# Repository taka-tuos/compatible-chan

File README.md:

# compatible-chan
[スタックチャン](https://github.com/stack-chan/stack-chan) 用の自由なCoreモジュール (GPLv3)

# ・ _ ・

# このプロジェクトのスコープ
- スタックチャンのCoreモジュールに自由な選択肢を追加することが目的
- M5Stack系の製品を広範に置き換えるもの**ではない** (スタックチャンに必要な機能のみを実装する)

# FAQ
## Q. M5Stackって「オープンハードウェア」では？
A. 各種ピン仕様や回路図こそオープンではあるが、シェルのCADデータやガーバーファイル、BOM等が公開されていないので「自由」ではない(と自分は考えている)。

## Q. 自由でないと何がダメ？
A. スタックチャンは「サ終とともに死ぬロボットはアカン(意訳)」という思想を含んでいて[^1](https://protopedia.net/prototype/2345)、M5Stackの供給が止まると死ぬ状況はよろしくないはず。  
(実際オンラインに依存していない旧AIBOシリーズでも、部品供給が無いのでバタバタ死んでいる)  
またM5Stackの仕様に縛られる状況でその打開ができないのもよろしくない(よく挙がる例としてはスピーカーとマイクが排他なことなど)

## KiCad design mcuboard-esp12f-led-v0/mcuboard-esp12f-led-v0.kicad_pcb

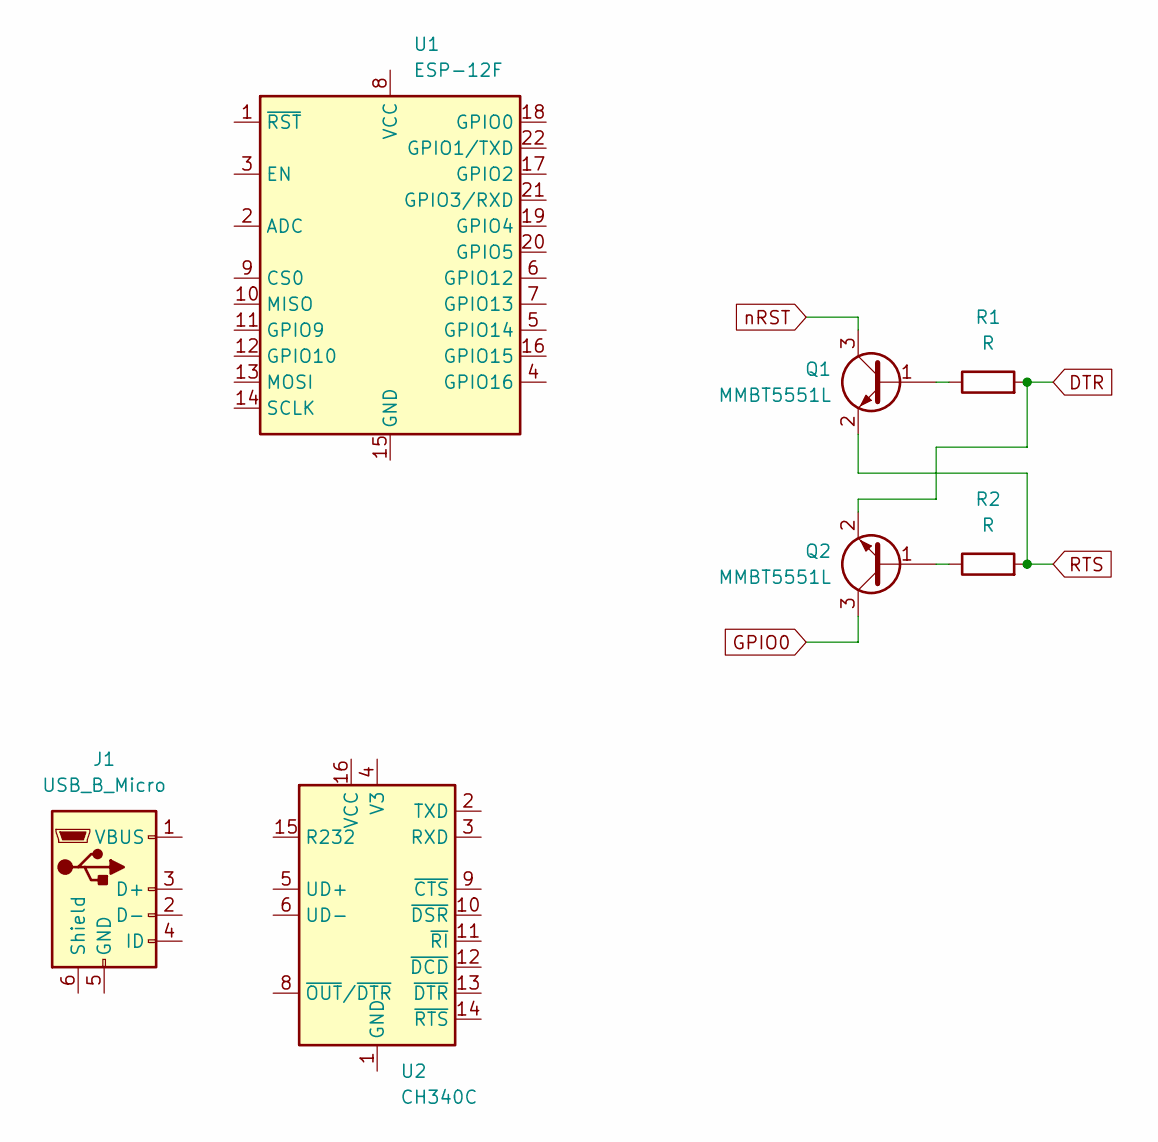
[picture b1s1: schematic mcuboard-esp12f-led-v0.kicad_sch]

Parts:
J1: USB_B_Micro; USB_Micro-B_Wuerth_629105150521
Q1, Q2: MMBT5551L; SOT-23
R1, R2: R; R_0805_2012Metric_Pad1.20x1.40mm_HandSolder
U1: ESP-12F; ESP-12E
U2: CH340C; SOIC-16_3.9x9.9mm_P1.27mm

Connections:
DTR: Q2.2 (E), R1.2
GPIO0: Q2.3 (C)
unnamed: Q1.1 (B), R1.1
unnamed: Q2.1 (B), R2.1
RTS: Q1.2 (E), R2.2
nRST: Q1.3 (C)

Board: 2 copper layers, 7 parts (0 on the bottom side), 4 nets, no tracks yet.

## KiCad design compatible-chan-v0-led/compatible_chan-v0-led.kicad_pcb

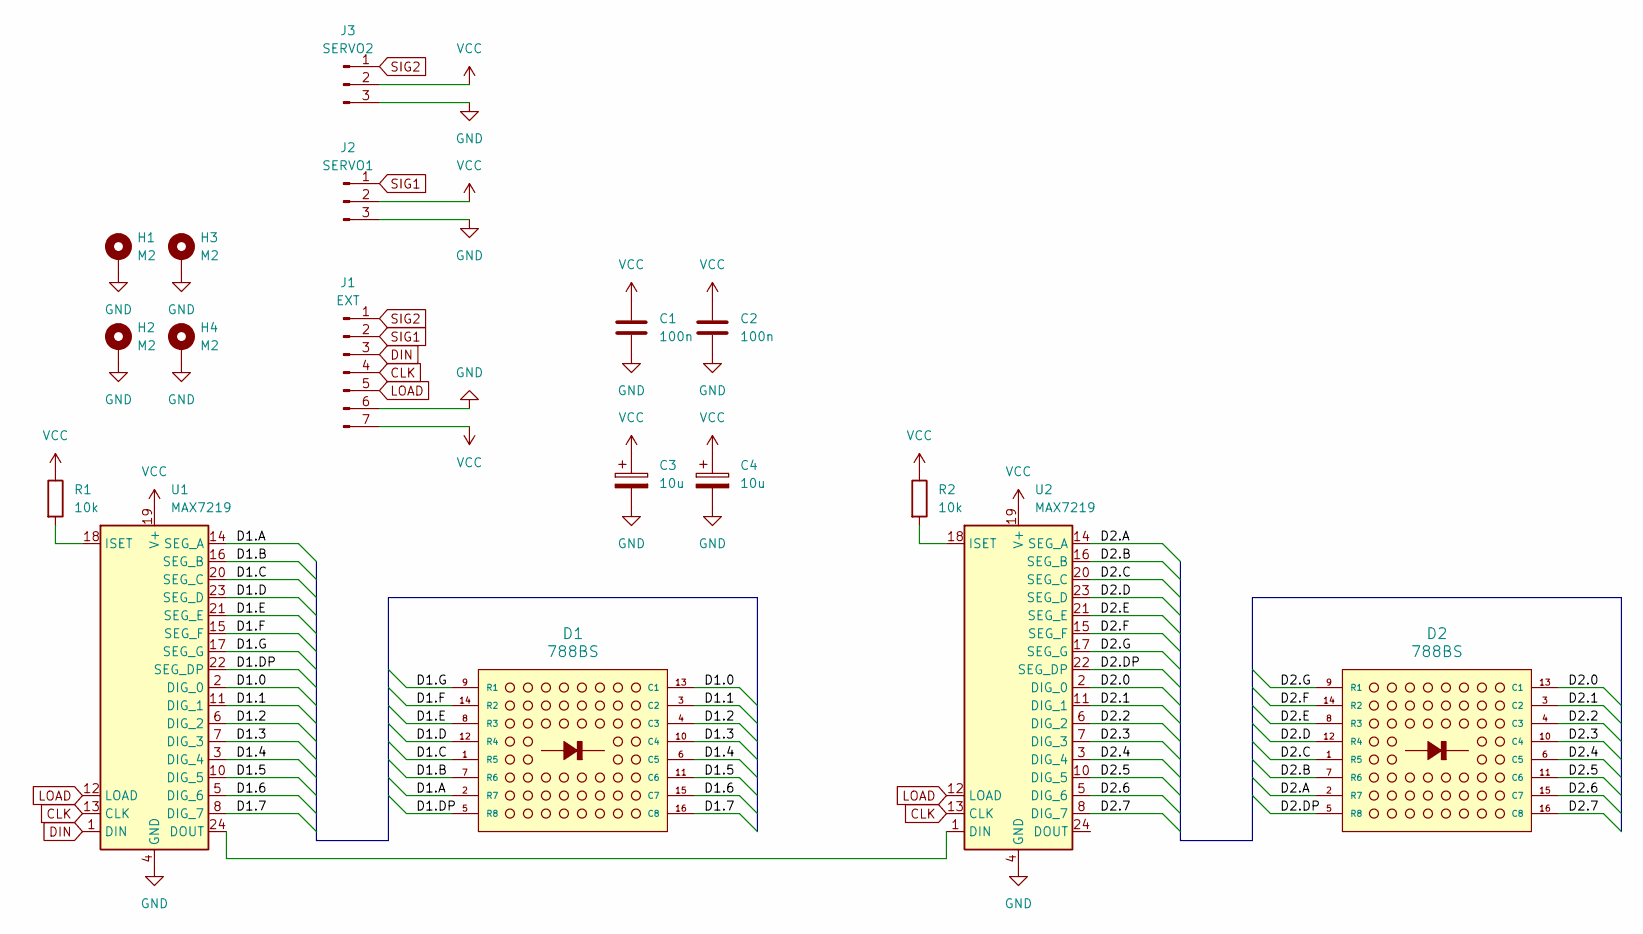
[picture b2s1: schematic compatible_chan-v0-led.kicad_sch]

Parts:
C1, C2: 100n; C_0805_2012Metric_Pad1.18x1.45mm_HandSolder
C3, C4: 10u; CP_EIA-2012-15_AVX-P_Pad1.30x1.05mm_HandSolder
D1, D2: 788BS; LED_8x8_1.9MM_20x20MM
H1, H2, H3, H4: M2; MountingHole_2.2mm_M2_DIN965_Pad
J1: EXT; PinHeader_1x07_P2.54mm_Horizontal
J2: SERVO1; PinHeader_1x03_P2.54mm_Vertical
J3: SERVO2; PinHeader_1x03_P2.54mm_Vertical
R1, R2: 10k; R_Axial_DIN0207_L6.3mm_D2.5mm_P10.16mm_Horizontal
U1, U2: MAX7219; SOIC-24W_7.5x15.4mm_P1.27mm

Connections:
/D1.0: D1.13 (C1), U1.2 (DIG_0)
/D1.1: D1.3 (C2), U1.11 (DIG_1)
/D1.2: D1.4 (C3), U1.6 (DIG_2)
/D1.3: D1.10 (C4), U1.7 (DIG_3)
/D1.4: D1.6 (C5), U1.3 (DIG_4)
/D1.5: D1.11 (C6), U1.10 (DIG_5)
/D1.6: D1.15 (C7), U1.5 (DIG_6)
/D1.7: D1.16 (C8), U1.8 (DIG_7)
/D1.A: D1.2 (R7), U1.14 (SEG_A)
/D1.B: D1.7 (R6), U1.16 (SEG_B)
/D1.C: D1.1 (R5), U1.20 (SEG_C)
/D1.D: D1.12 (R4), U1.23 (SEG_D)
/D1.DP: D1.5 (R8), U1.22 (SEG_DP)
/D1.E: D1.8 (R3), U1.21 (SEG_E)
/D1.F: D1.14 (R2), U1.15 (SEG_F)
/D1.G: D1.9 (R1), U1.17 (SEG_G)
/D2.0: D2.13 (C1), U2.2 (DIG_0)
/D2.1: D2.3 (C2), U2.11 (DIG_1)
/D2.2: D2.4 (C3), U2.6 (DIG_2)
/D2.3: D2.10 (C4), U2.7 (DIG_3)
/D2.4: D2.6 (C5), U2.3 (DIG_4)
/D2.5: D2.11 (C6), U2.10 (DIG_5)
/D2.6: D2.15 (C7), U2.5 (DIG_6)
/D2.7: D2.16 (C8), U2.8 (DIG_7)
/D2.A: D2.2 (R7), U2.14 (SEG_A)
/D2.B: D2.7 (R6), U2.16 (SEG_B)
/D2.C: D2.1 (R5), U2.20 (SEG_C)
/D2.D: D2.12 (R4), U2.23 (SEG_D)
/D2.DP: D2.5 (R8), U2.22 (SEG_DP)
/D2.E: D2.8 (R3), U2.21 (SEG_E)
/D2.F: D2.14 (R2), U2.15 (SEG_F)
/D2.G: D2.9 (R1), U2.17 (SEG_G)
CLK: J1.4, U1.13 (CLK), U2.13 (CLK)
DIN: J1.3, U1.1 (DIN)
GND: C1.2, C2.2, C3.2, C4.2, H1.1, H2.1, H3.1, H4.1, J1.6, J2.3, J3.3, U1.4 (GND), U1.9 (GND), U2.4 (GND), U2.9 (GND)
LOAD: J1.5, U1.12 (LOAD), U2.12 (LOAD)
unnamed: U1.24 (DOUT), U2.1 (DIN)
unnamed: R1.2, U1.18 (ISET)
unnamed: R2.2, U2.18 (ISET)
SIG1: J1.2, J2.1
SIG2: J1.1, J3.1
VCC: C1.1, C2.1, C3.1, C4.1, J1.7, J2.2, J3.2, R1.1, R2.1, U1.19 (V+), U2.19 (V+)

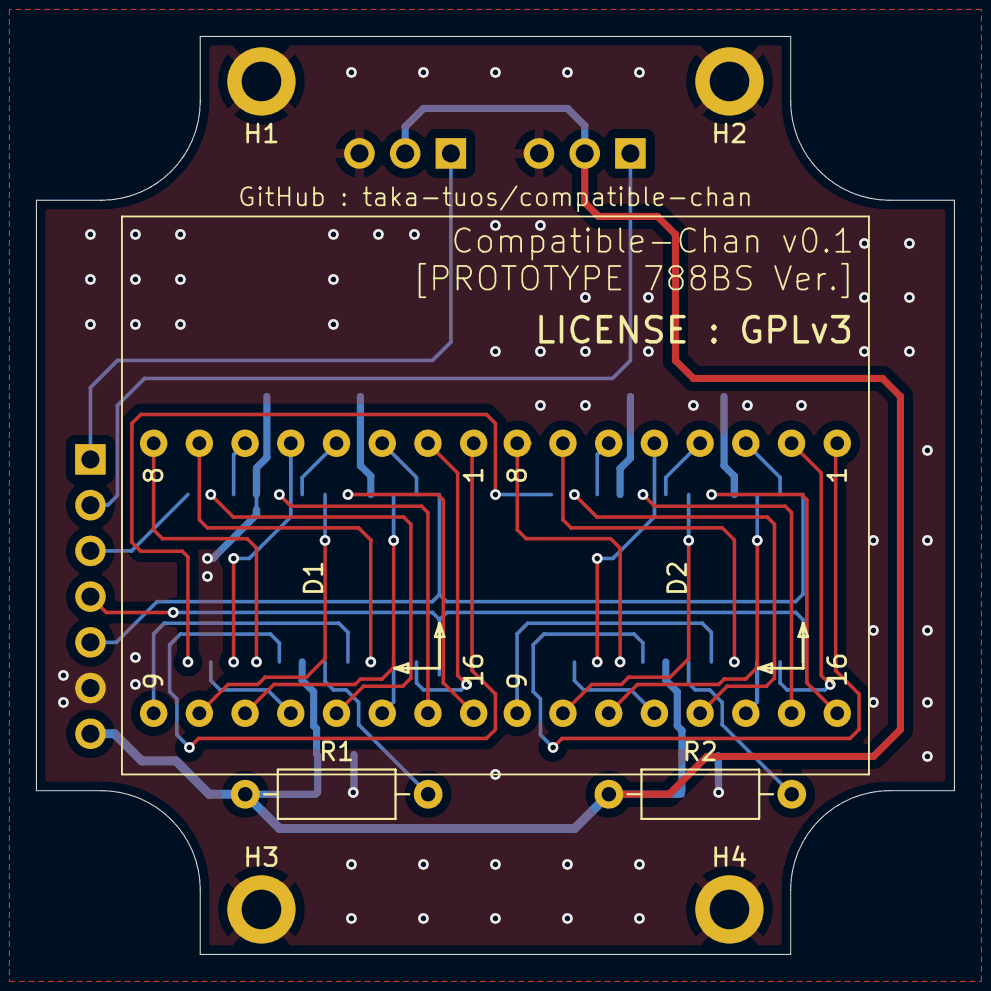
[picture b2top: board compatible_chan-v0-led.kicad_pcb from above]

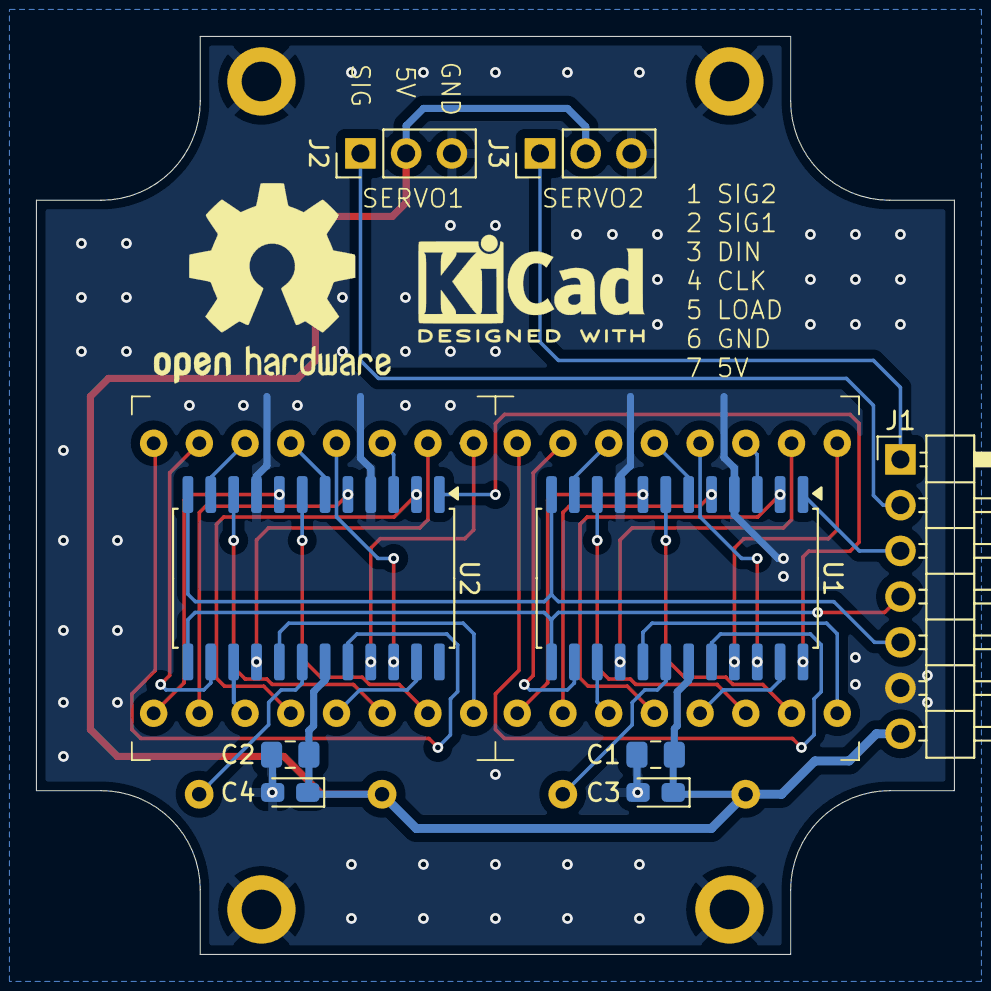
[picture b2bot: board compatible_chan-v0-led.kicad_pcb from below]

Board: 2 copper layers, 51.0 x 51.0 mm, 17 parts (9 on the bottom side), 42 nets.

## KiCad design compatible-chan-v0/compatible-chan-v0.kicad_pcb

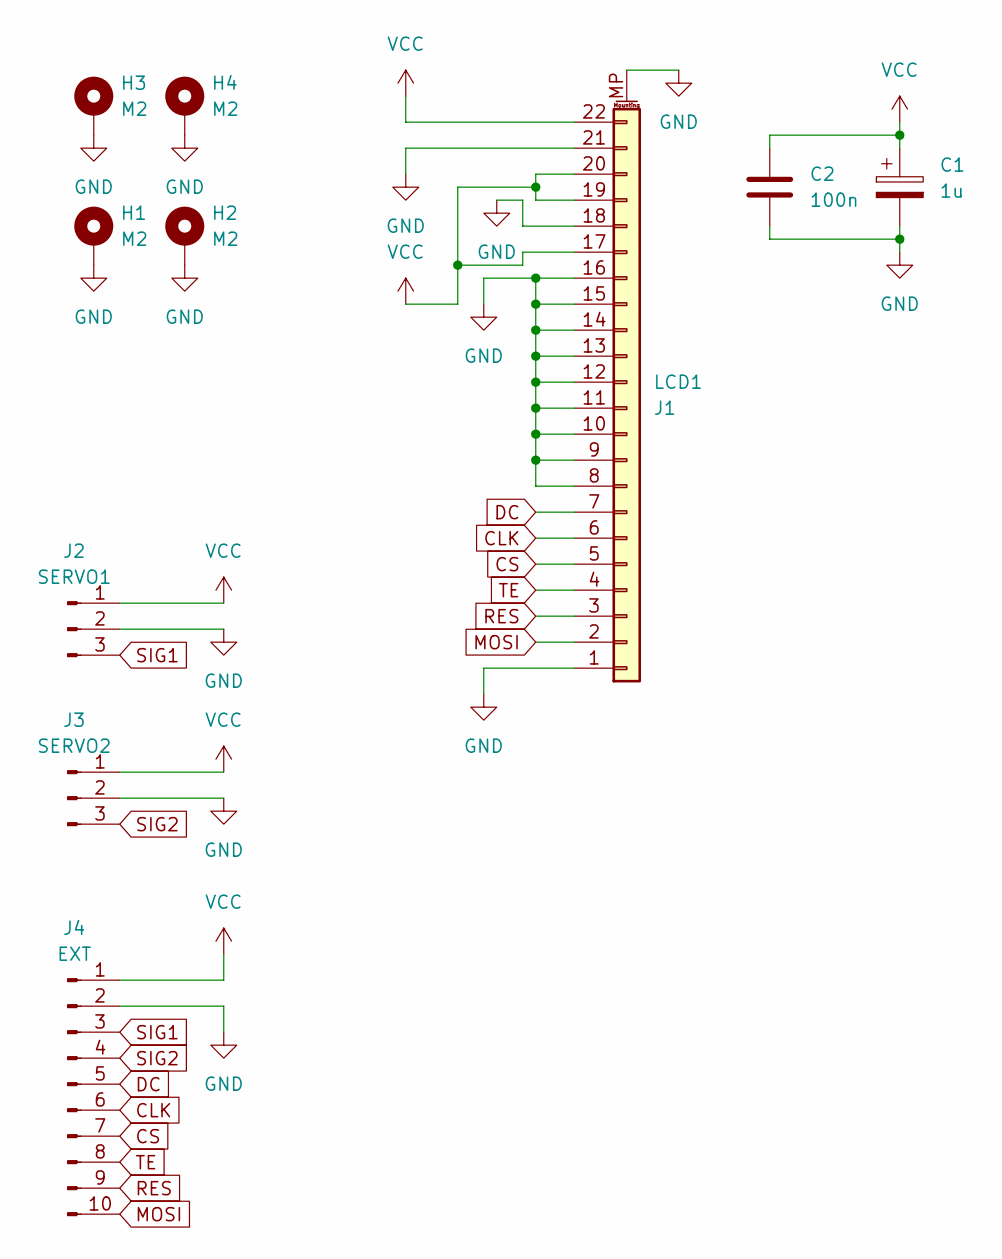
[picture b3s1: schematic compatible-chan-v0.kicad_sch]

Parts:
C1: 1u; CP_EIA-2012-12_Kemet-R_Pad1.30x1.05mm_HandSolder
C2: 100n; C_0805_2012Metric_Pad1.18x1.45mm_HandSolder
H1, H2, H3, H4: M2; MountingHole_2.2mm_M2_DIN965_Pad
J1: LCD1; TE_2-1734839-2_1x22-1MP_P0.5mm_Horizontal
J2: SERVO1; PinHeader_1x03_P2.54mm_Vertical
J3: SERVO2; PinHeader_1x03_P2.54mm_Vertical
J4: EXT; PinHeader_1x10_P2.54mm_Horizontal

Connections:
CLK: J1.6, J4.6
CS: J1.5, J4.7
DC: J1.7, J4.5
GND: C1.2, C2.2, H1.1, H2.1, H3.1, H4.1, J1.1, J1.8, J1.9, J1.10, J1.11, J1.12, J1.13, J1.14, J1.15, J1.16, J1.18, J1.21, J1.MP (MountPin), J2.2, J3.2, J4.2
MOSI: J1.2, J4.10
RES: J1.3, J4.9
SIG1: J2.3, J4.3
SIG2: J3.3, J4.4
TE: J1.4, J4.8
VCC: C1.1, C2.1, J1.17, J1.19, J1.20, J1.22, J2.1, J3.1, J4.1

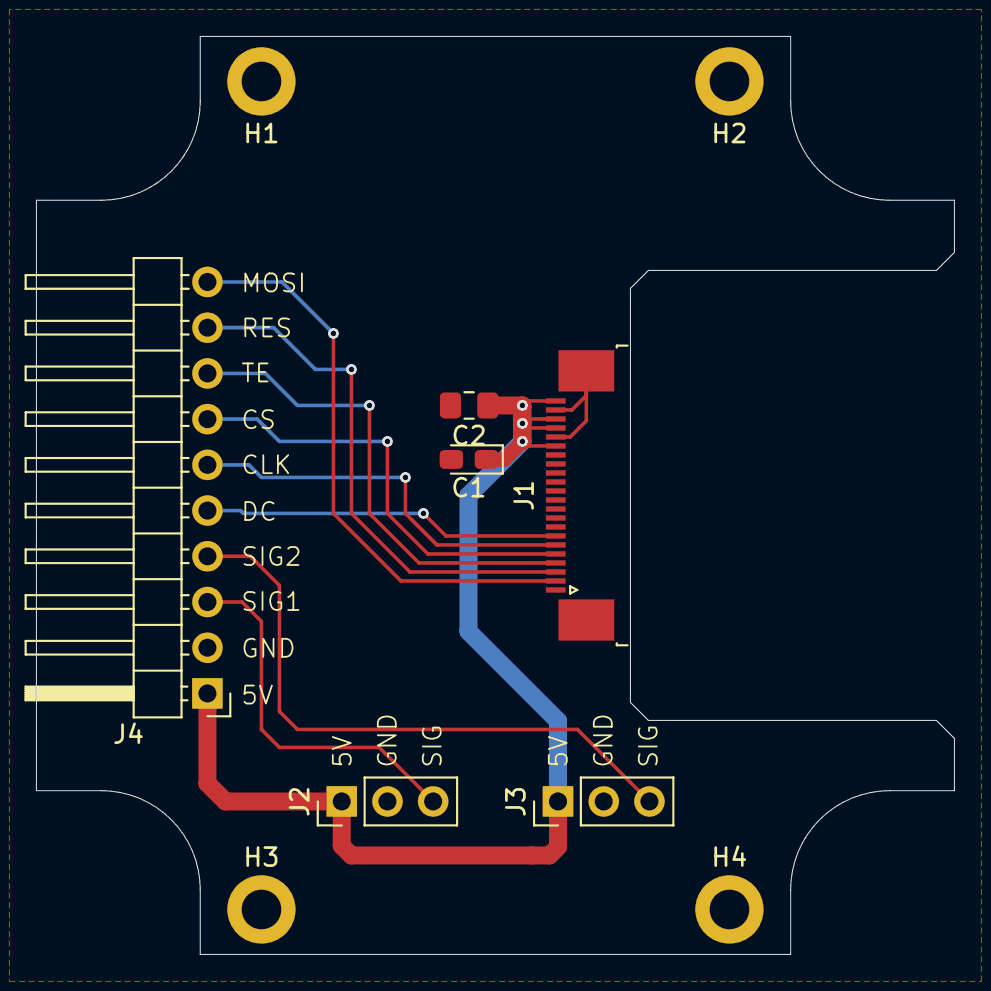
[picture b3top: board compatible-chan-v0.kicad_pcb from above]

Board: 2 copper layers, 51.0 x 51.0 mm, 10 parts (0 on the bottom side), 10 nets.

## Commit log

2024-07-31 first commit, v0基板etc追加
2024-07-31 README更新 Current Status削除
2024-08-01 LED版関連更新 基板更新,シェル設計
2024-08-01 READMEの文面を調整
2024-08-01 LED版調整 (#3) インサート穴再調整、フロント穴作成
2024-08-25 v0-led基板更新、テストファーム・v0.1用MCU基板追加
2024-08-25 README更新
2024-08-25 ファームウェア更新

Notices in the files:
compatible-chan-v0-led/compatible_chan-v0-led.kicad_pcb:
LICENSE : GPLv3
